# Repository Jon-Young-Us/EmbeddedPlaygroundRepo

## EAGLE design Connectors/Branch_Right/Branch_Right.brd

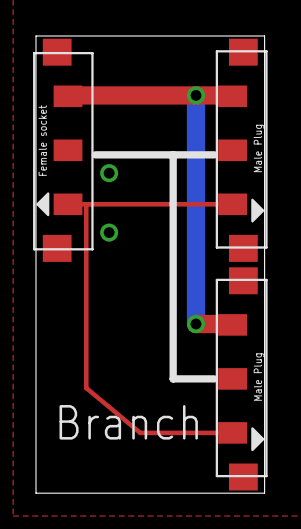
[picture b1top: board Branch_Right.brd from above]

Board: 2 copper layers, 12.7 x 25.4 mm, 3 parts (0 on the bottom side), 3 nets.

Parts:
U$1, U$4: CONN-PLUG-3POS-3MM; PLUG-3POS-3MM-SMD
U$2: CONN-SOCKET-3POS-3MM; SOCKET-3POS-3MM-SMD

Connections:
GND: U$1.GND, U$2.GND, U$4.GND
VCC: U$1.VCC, U$2.VCC, U$4.VCC
Y: U$1.SIG-OUT, U$2.SIG-IN, U$4.SIG-OUT

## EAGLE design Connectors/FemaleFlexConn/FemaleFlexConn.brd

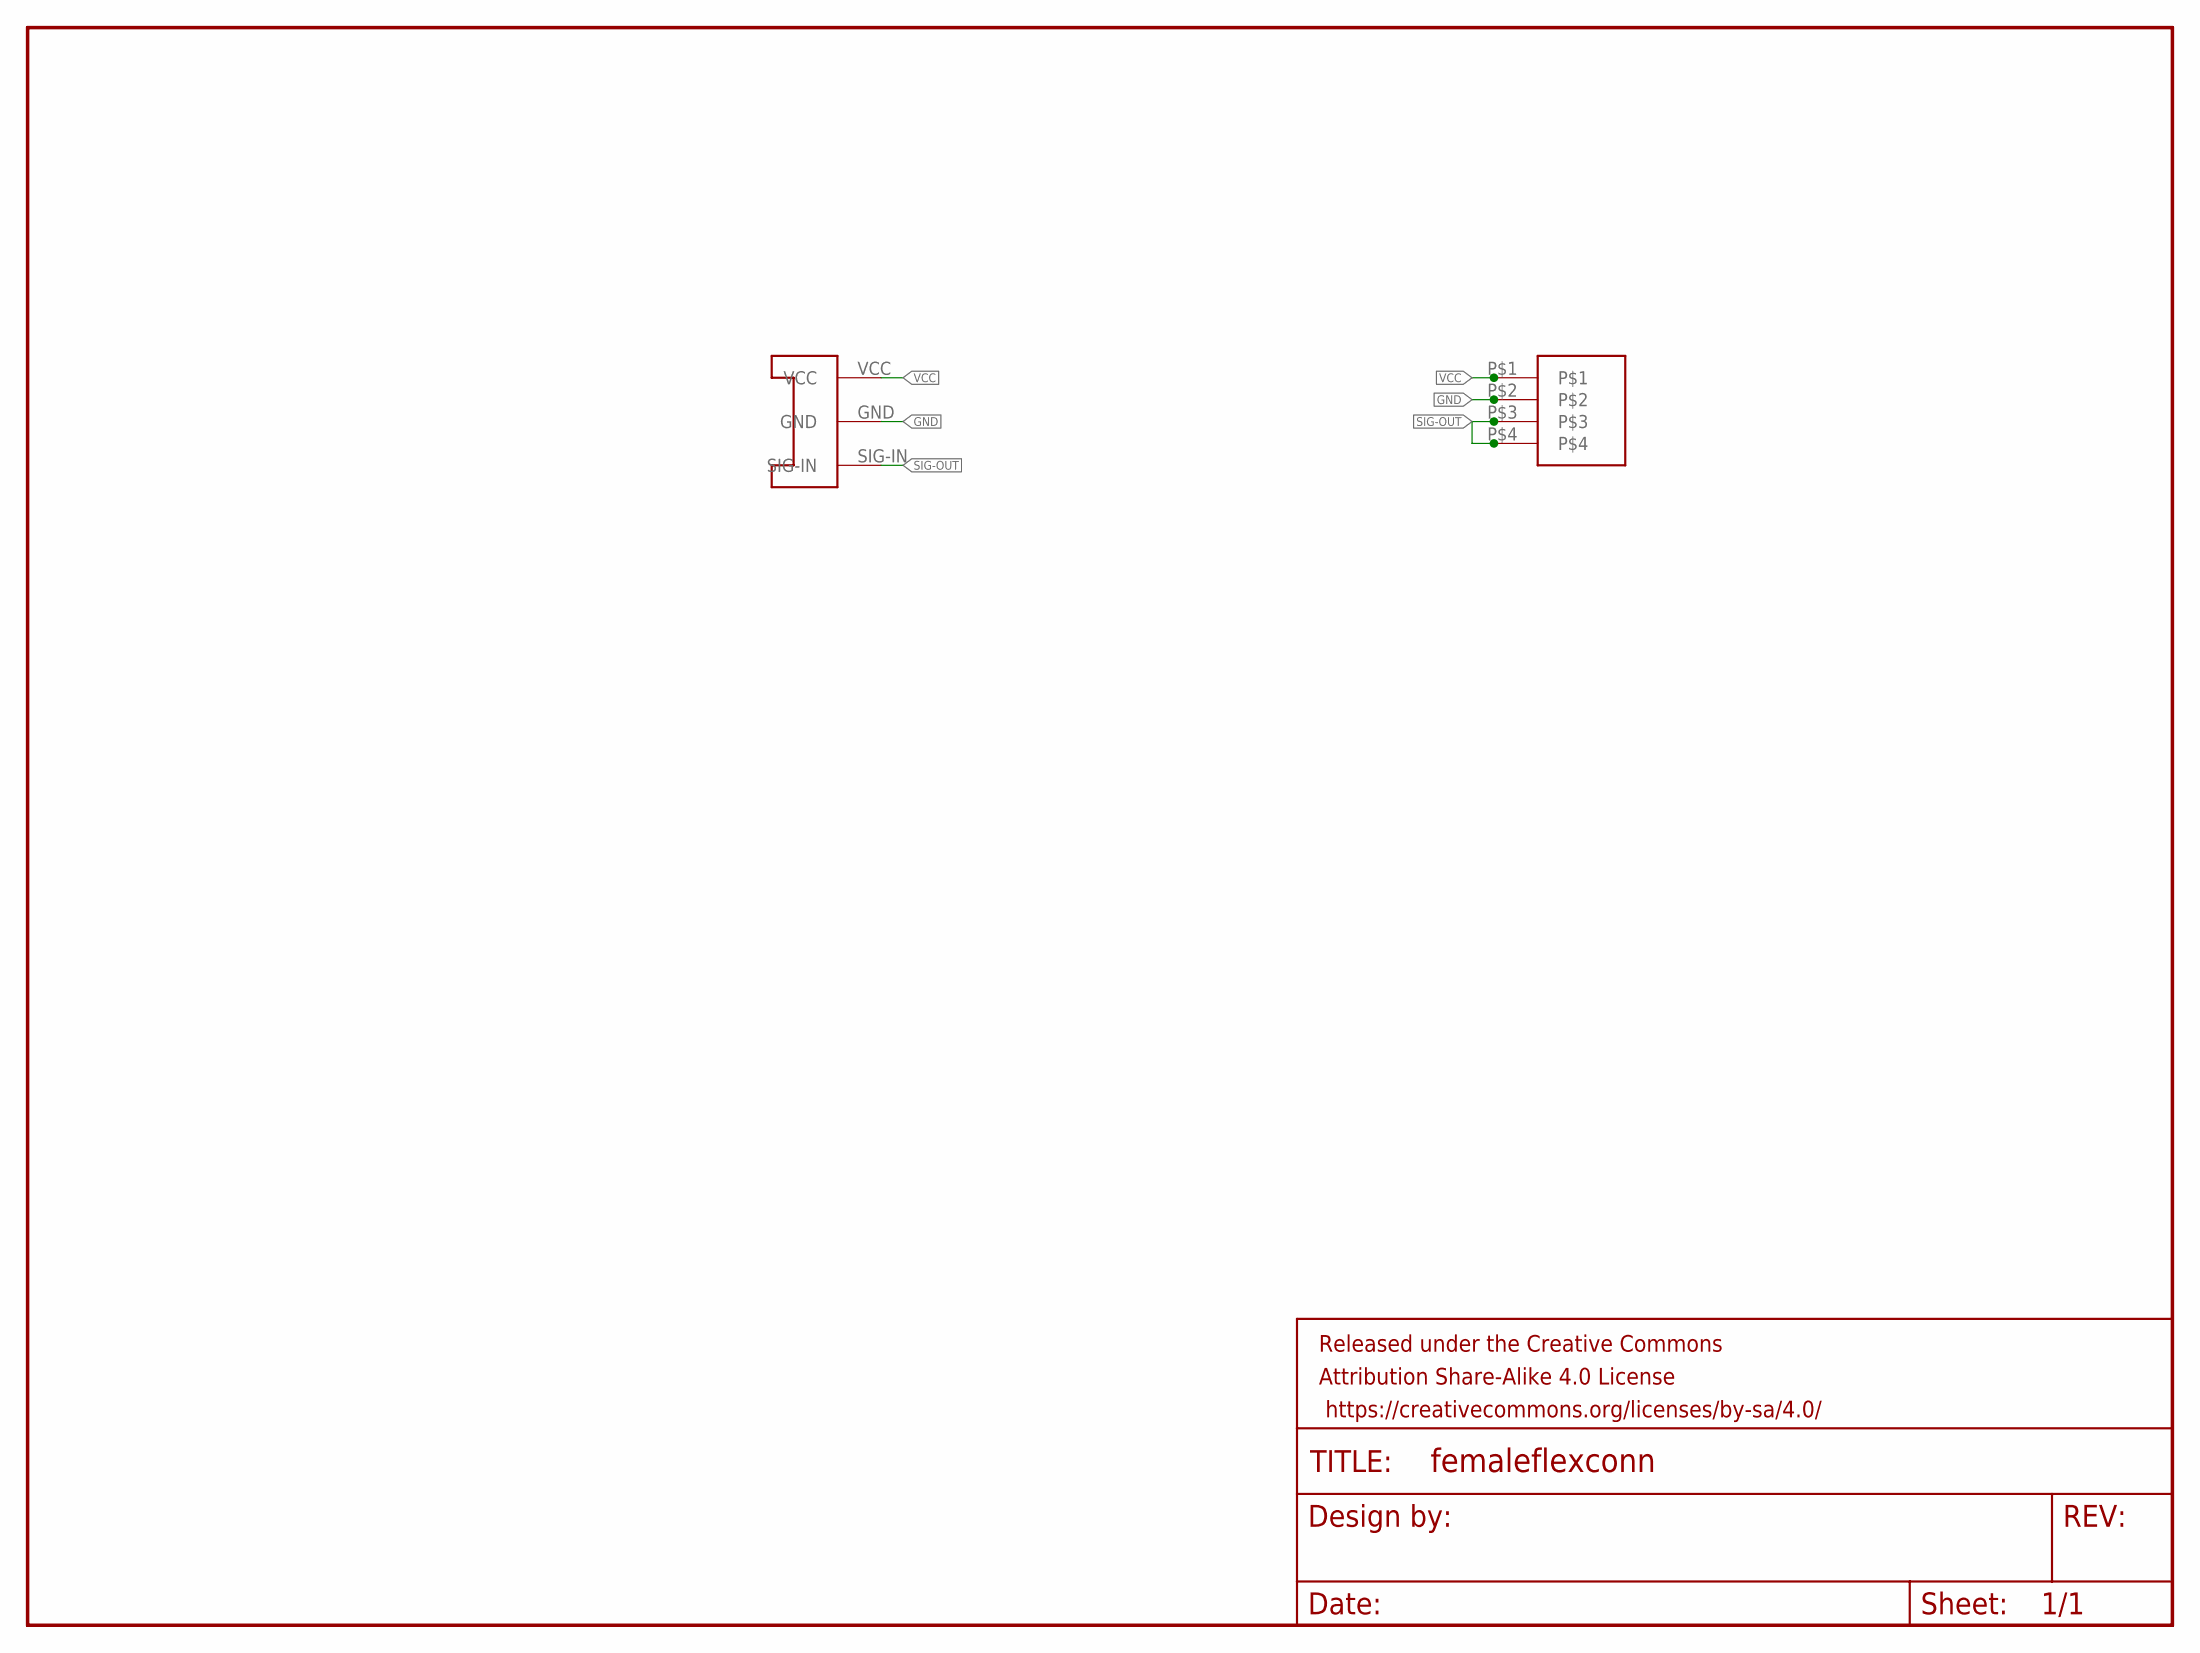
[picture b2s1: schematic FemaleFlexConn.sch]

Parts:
FRAME1: FRAME-LETTERNO_PACKAGE; DUMMY
U$1: CONN-RCPT-BLADE-4POS-4MM; RECEPT-BLAD-4MM-SMD
U$2: CONN-SOCKET-3POS-3MM; SOCKET-3POS-3MM-SMD

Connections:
GND: U$1.P$2, U$2.GND
SIG-OUT: U$1.P$3, U$1.P$4, U$2.SIG-IN
VCC: U$1.P$1, U$2.VCC

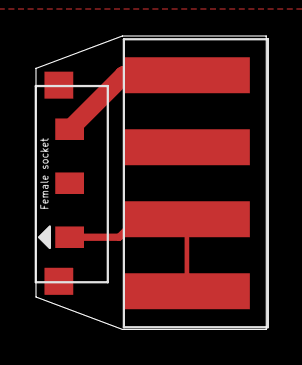
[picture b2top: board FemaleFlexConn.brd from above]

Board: 2 copper layers, 12.8 x 16.3 mm, 3 parts (0 on the bottom side), 3 nets.

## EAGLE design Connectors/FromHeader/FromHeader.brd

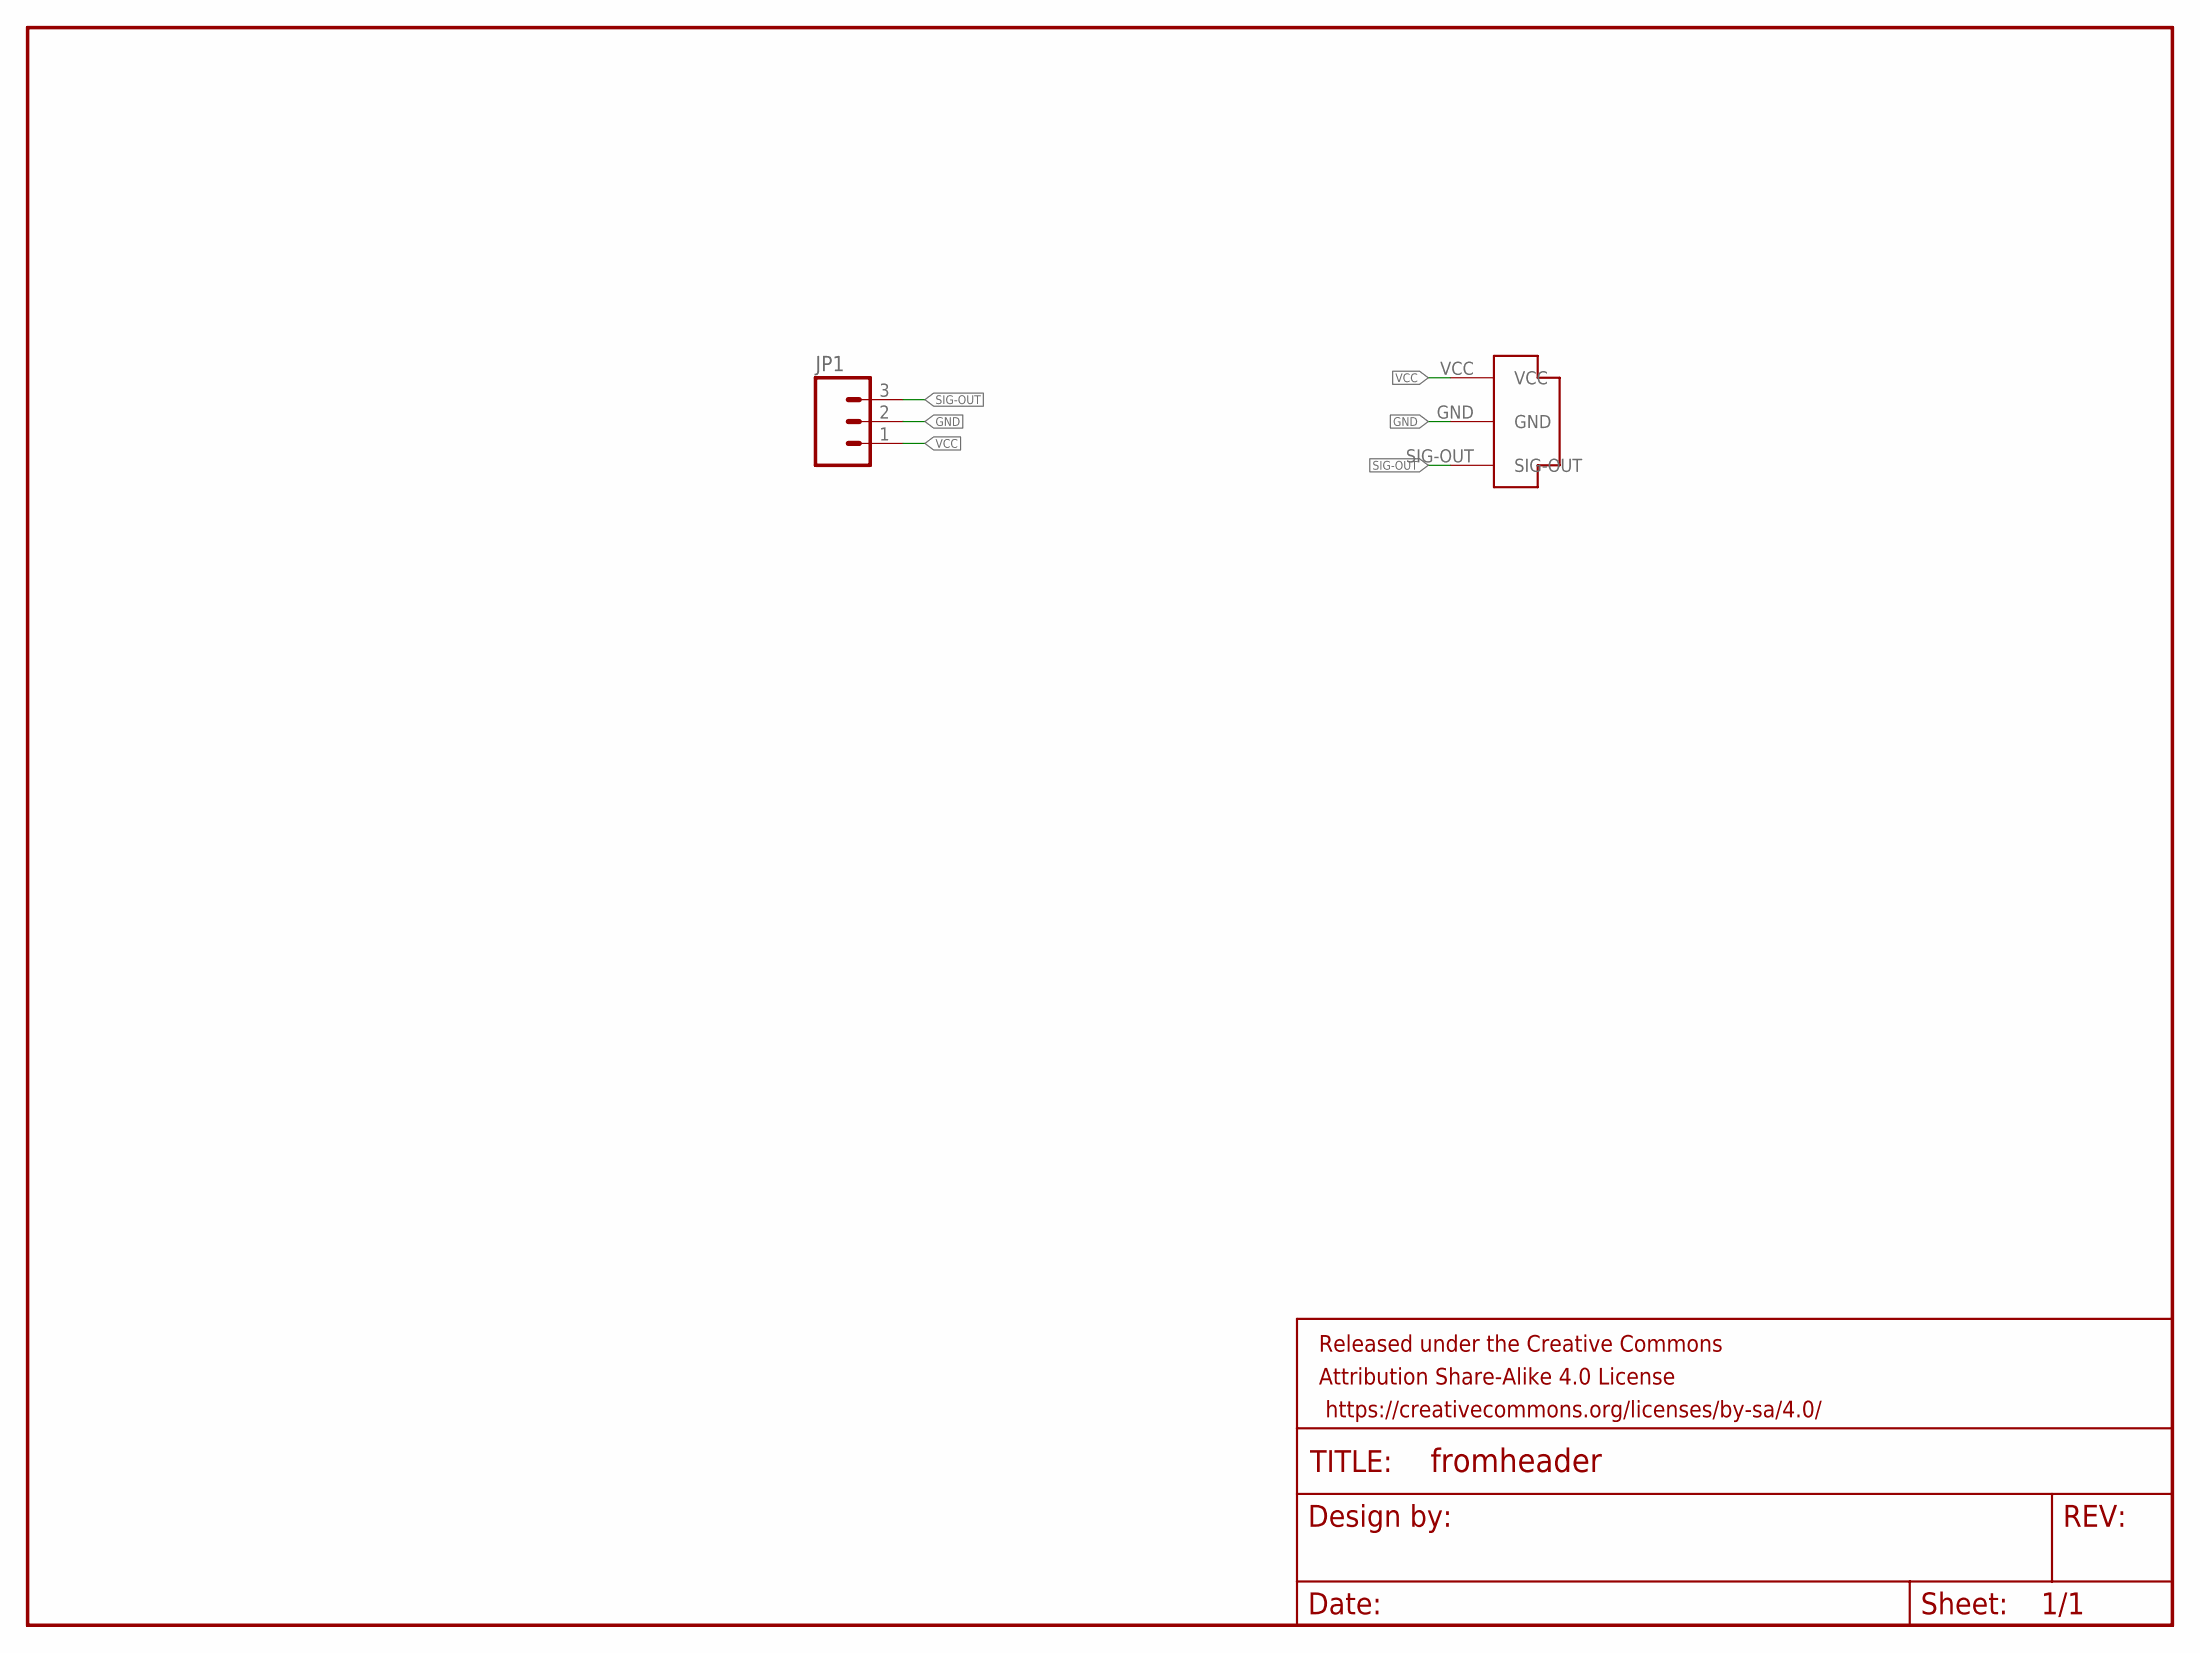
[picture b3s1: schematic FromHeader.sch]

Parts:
FRAME1: FRAME-LETTERNO_PACKAGE; DUMMY
JP1: M03LOCK; 1X03_LOCK
U$1: CONN-PLUG-3POS-3MM; PLUG-3POS-3MM-SMD

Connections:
GND: JP1.2, U$1.GND
SIG-OUT: JP1.3, U$1.SIG-OUT
VCC: JP1.1, U$1.VCC

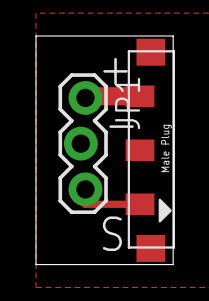
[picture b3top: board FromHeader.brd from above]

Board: 2 copper layers, 7.6 x 12.7 mm, 3 parts (0 on the bottom side), 3 nets.

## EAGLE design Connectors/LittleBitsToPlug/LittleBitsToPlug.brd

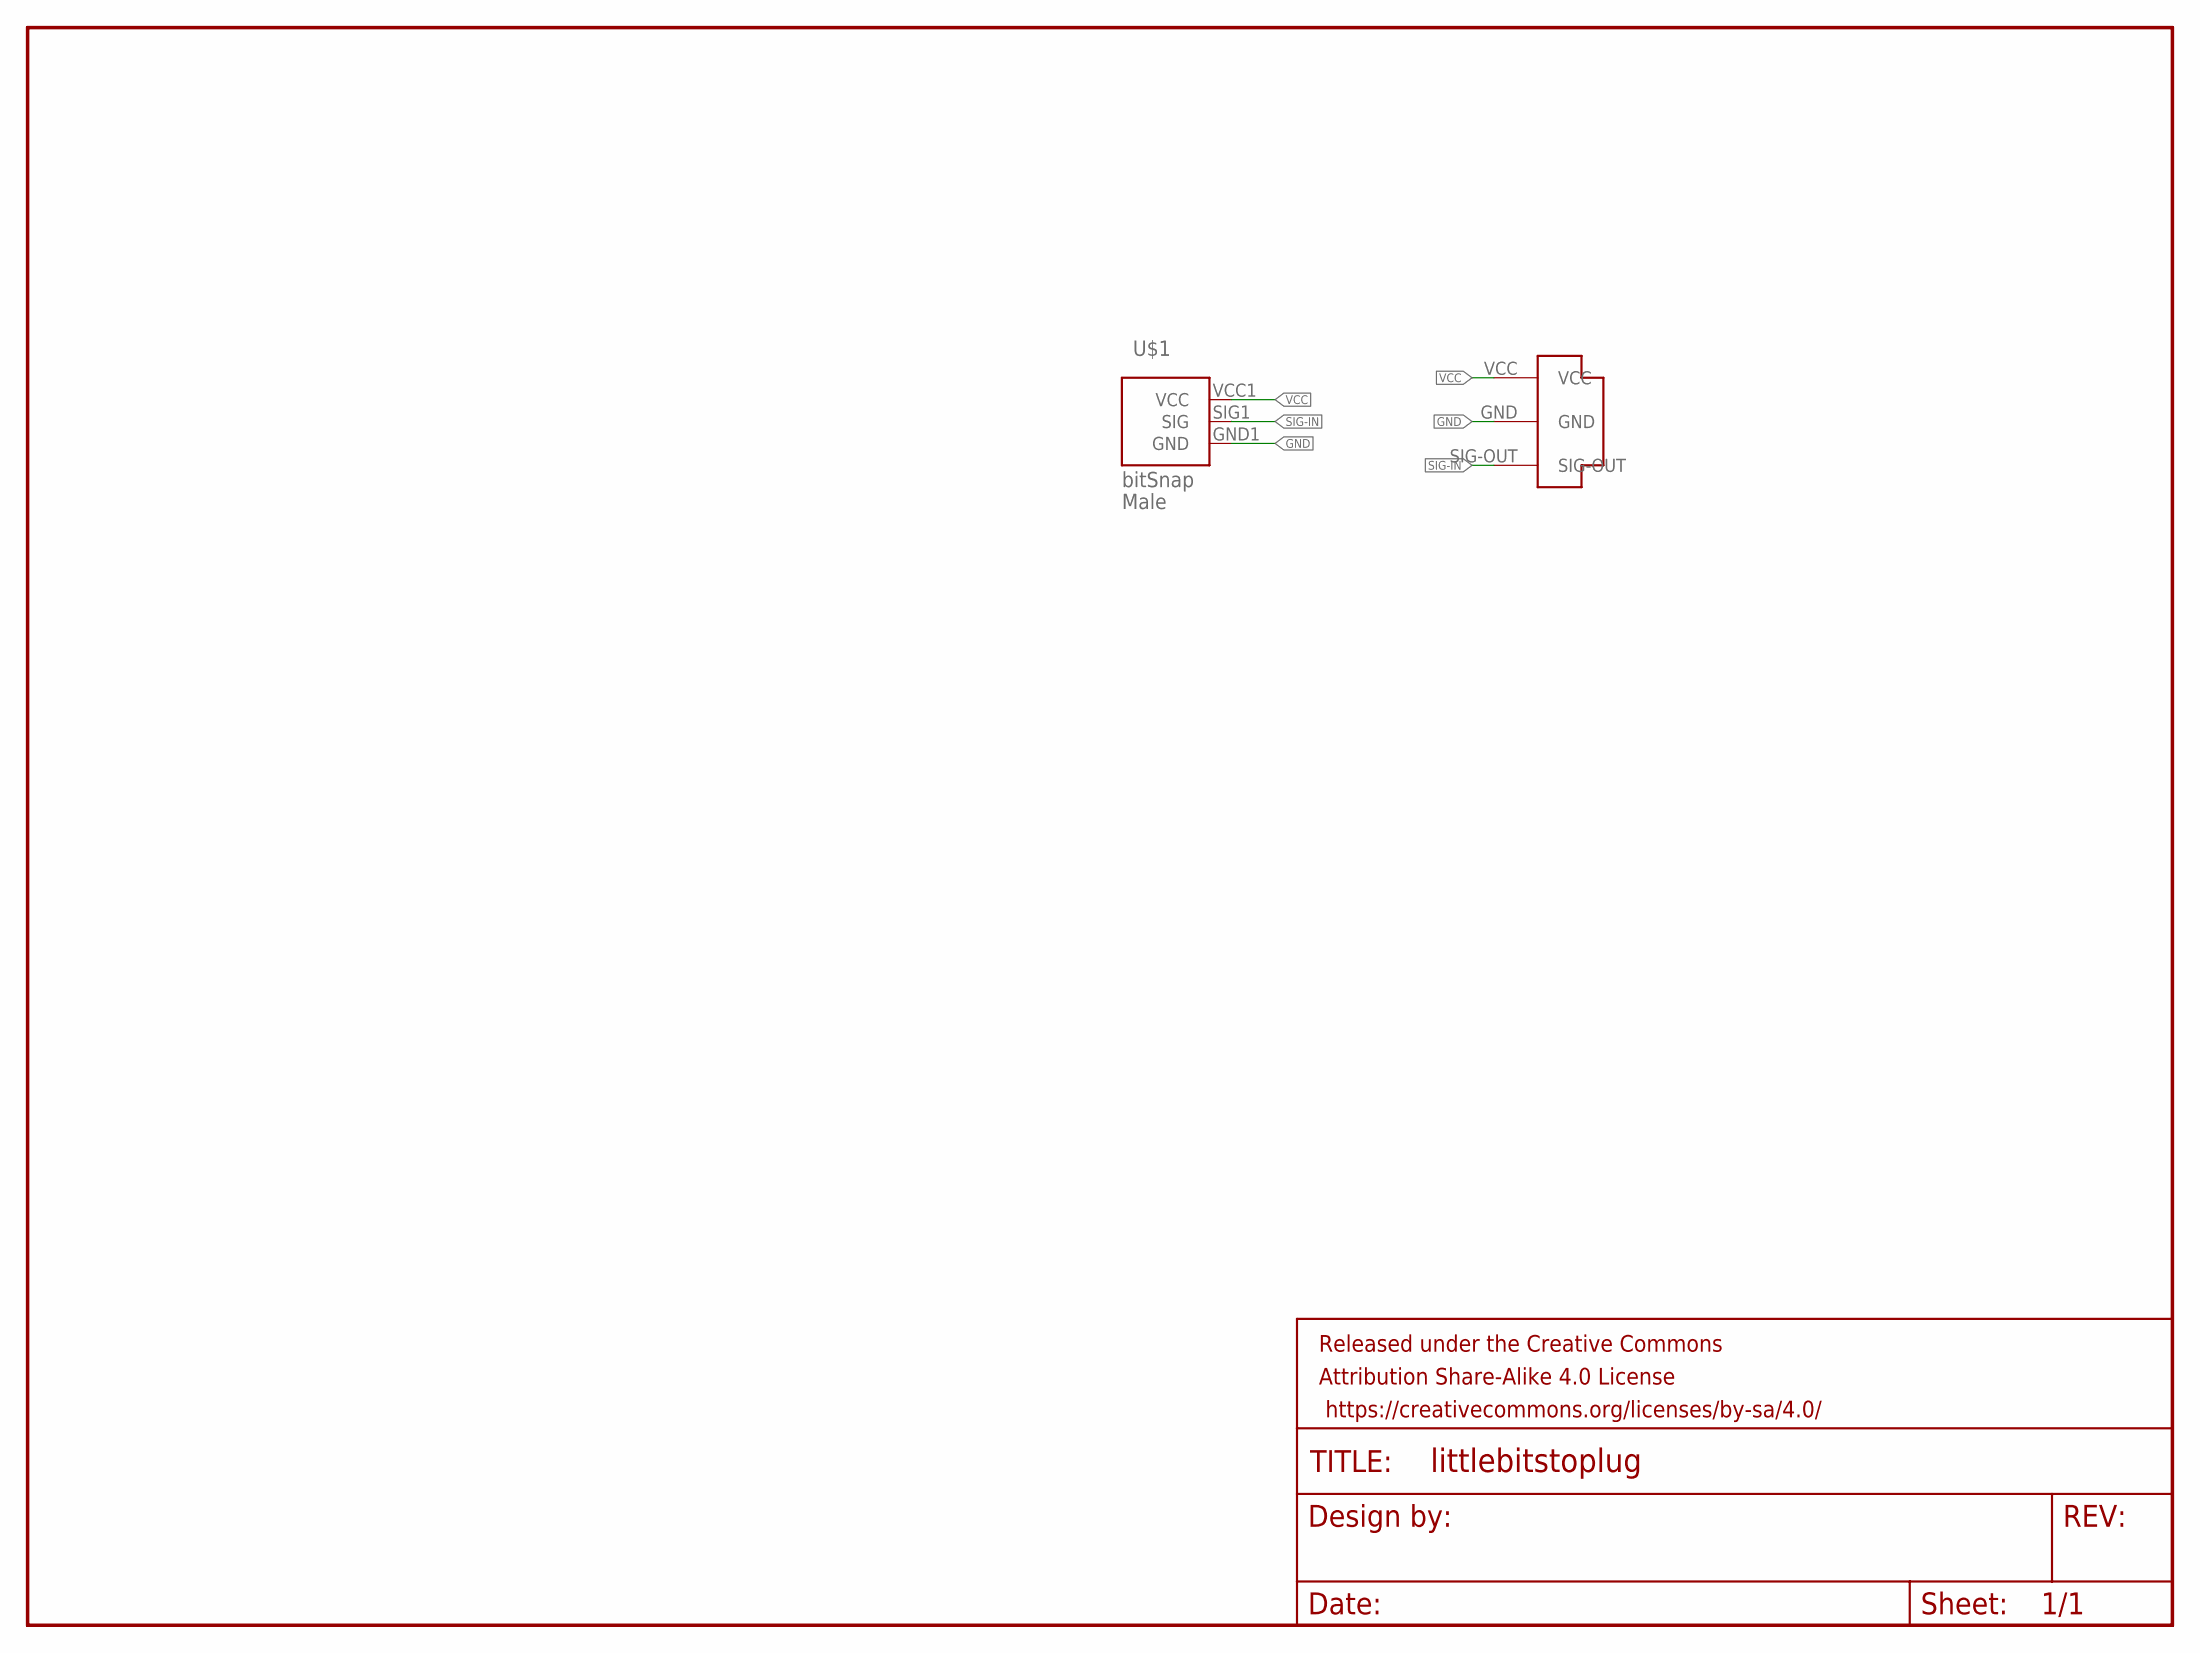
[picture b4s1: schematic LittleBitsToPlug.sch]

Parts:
FRAME1: FRAME-LETTERNO_PACKAGE; DUMMY
U$1: BITSNAP_V03_MALE
U$2: CONN-PLUG-3POS-3MM; PLUG-3POS-3MM-SMD

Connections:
GND: U$1.GND1 (GND), U$2.GND
SIG-IN: U$1.SIG1 (SIG), U$2.SIG-OUT
VCC: U$1.VCC1 (VCC), U$2.VCC

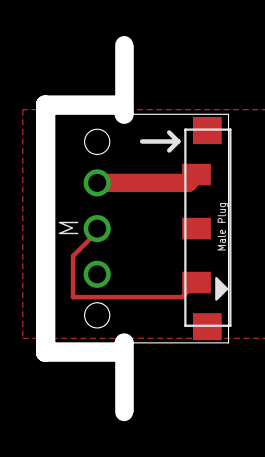
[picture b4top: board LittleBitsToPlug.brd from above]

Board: 2 copper layers, 9.7 x 12.7 mm, 3 parts (0 on the bottom side), 3 nets.

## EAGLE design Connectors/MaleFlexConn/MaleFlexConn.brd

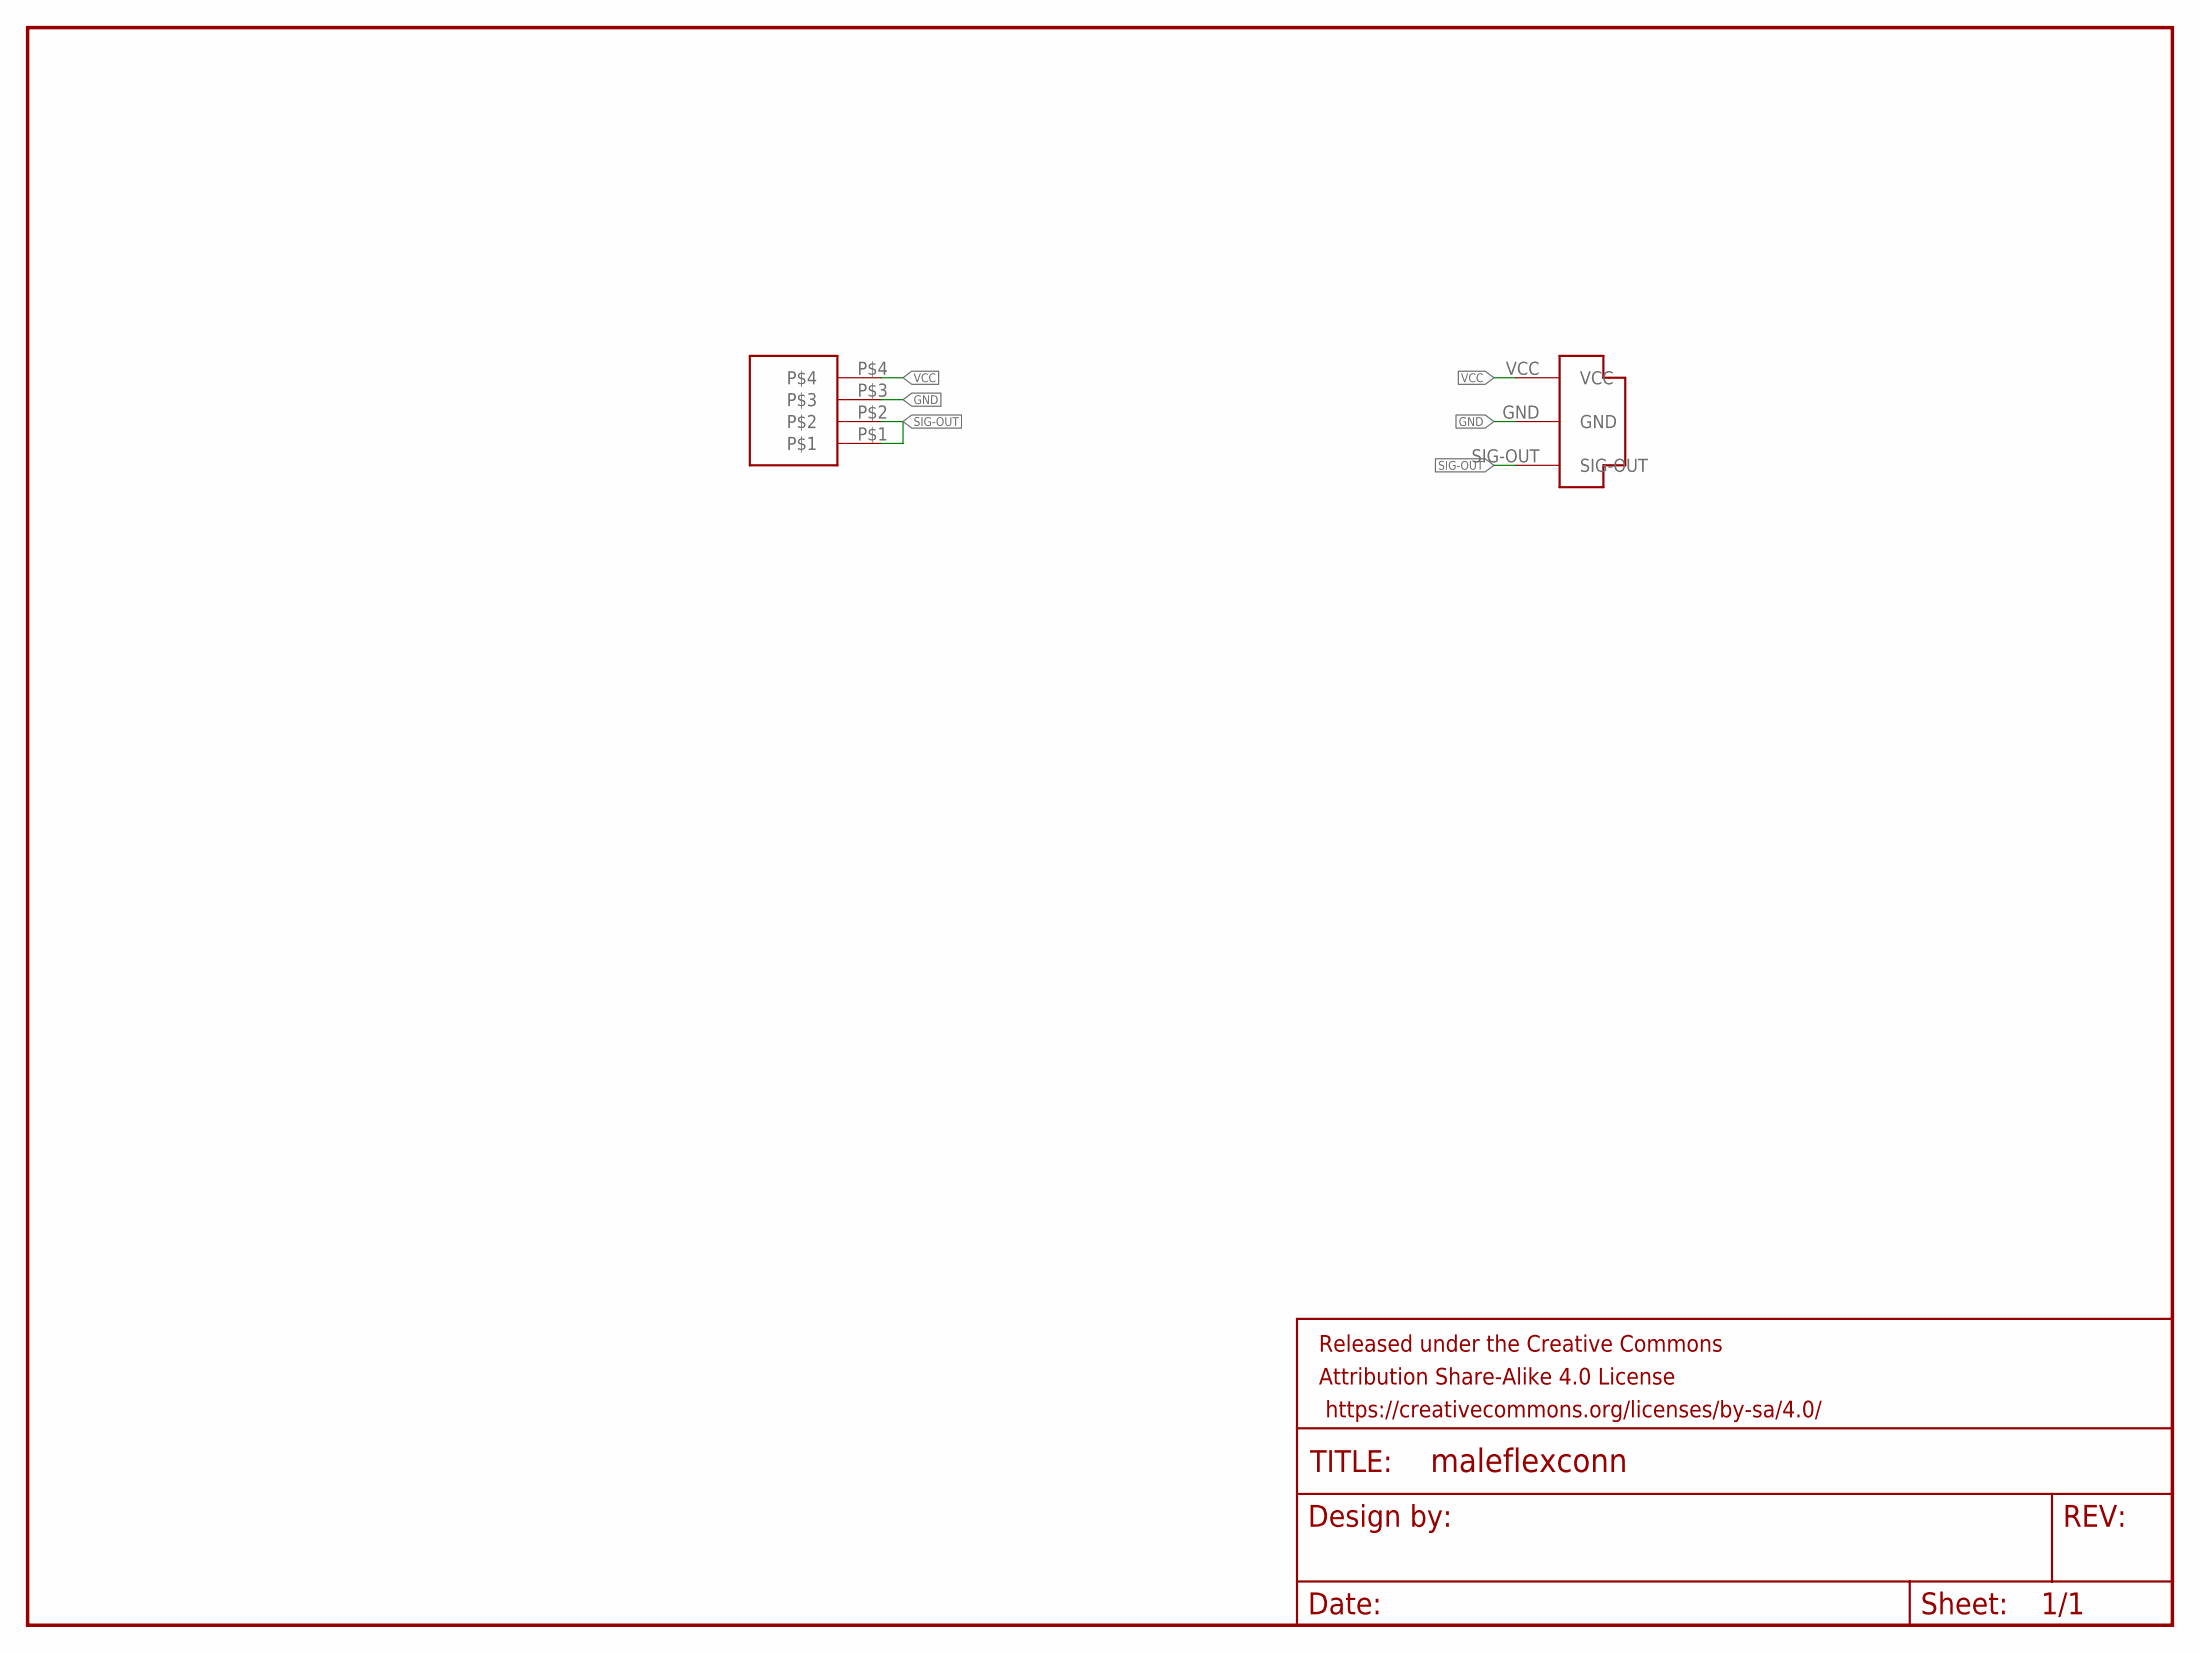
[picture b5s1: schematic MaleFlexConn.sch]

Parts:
FRAME1: FRAME-LETTERNO_PACKAGE; DUMMY
U$1: CONN-PLUG-3POS-3MM; PLUG-3POS-3MM-SMD
U$2: CONN-RCPT-BLADE-4POS-4MM; RECEPT-BLAD-4MM-SMD

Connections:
GND: U$1.GND, U$2.P$3
SIG-OUT: U$1.SIG-OUT, U$2.P$1, U$2.P$2
VCC: U$1.VCC, U$2.P$4

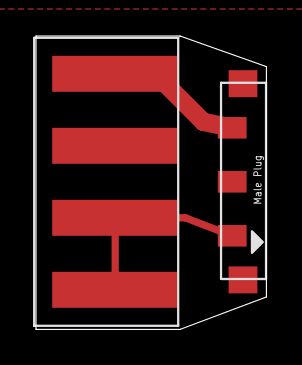
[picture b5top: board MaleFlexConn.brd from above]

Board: 2 copper layers, 12.8 x 16.3 mm, 3 parts (0 on the bottom side), 3 nets.

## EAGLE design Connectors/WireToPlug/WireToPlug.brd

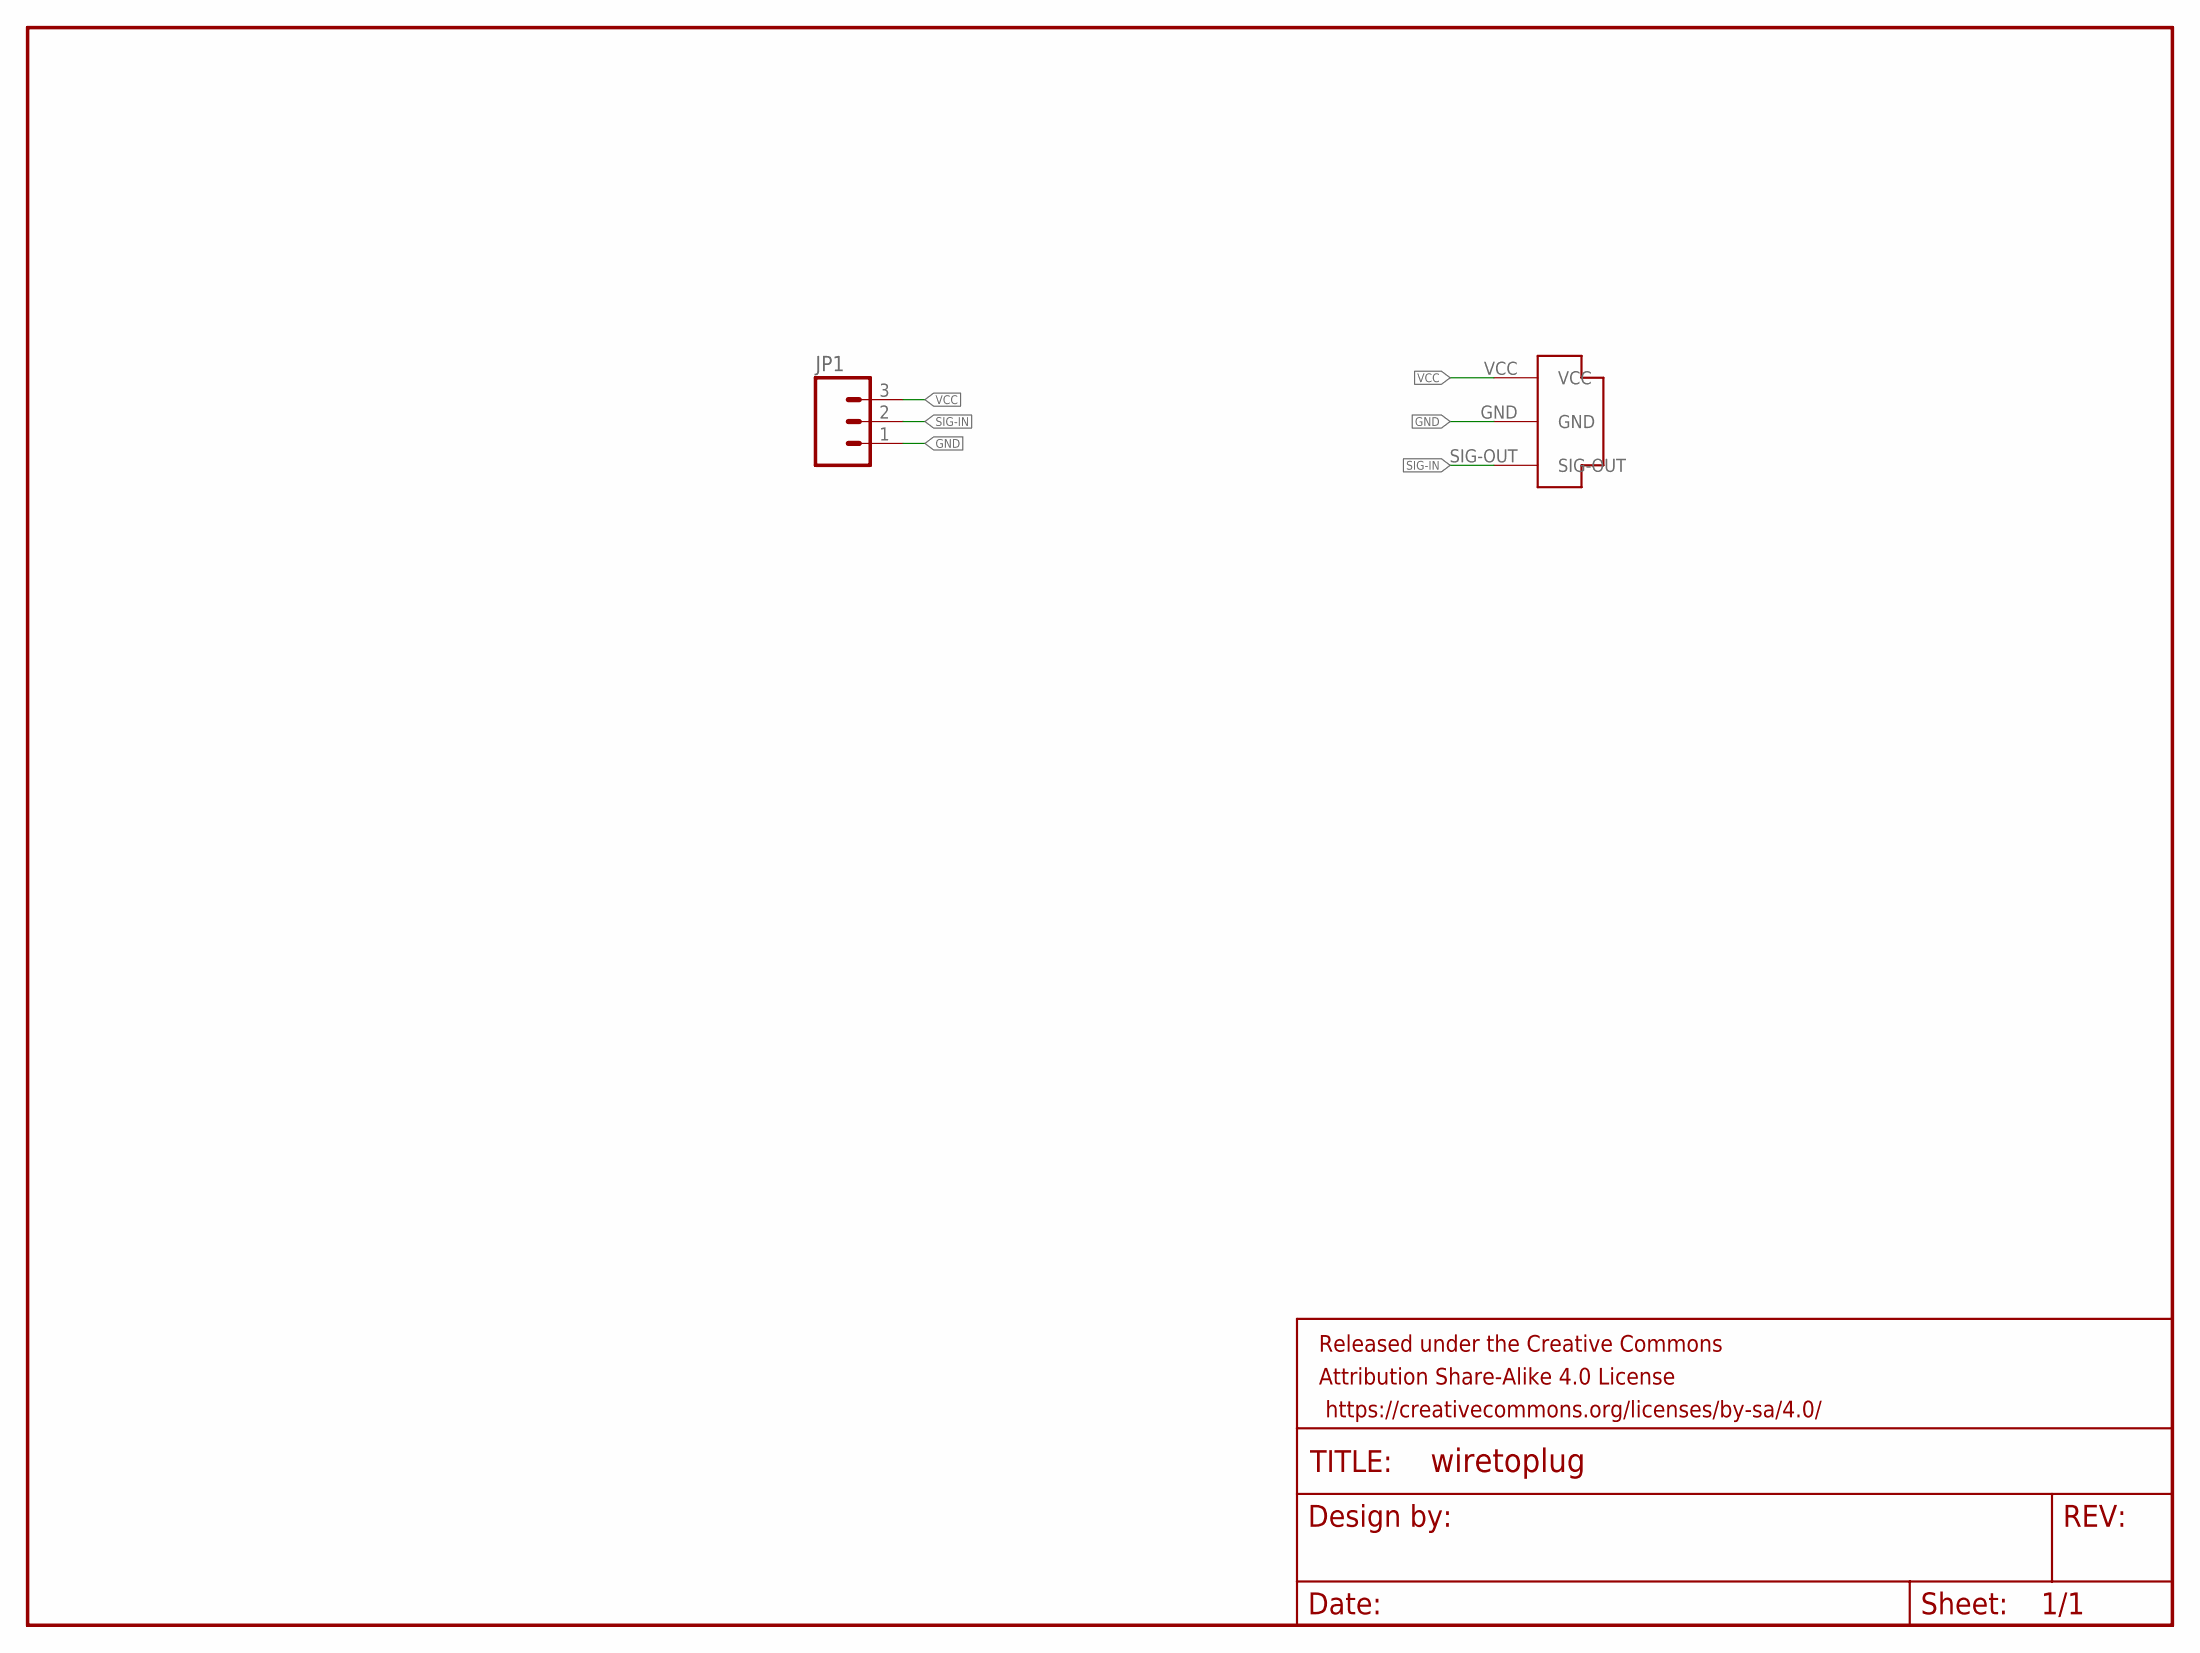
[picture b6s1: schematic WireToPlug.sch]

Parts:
FRAME1: FRAME-LETTERNO_PACKAGE; DUMMY
JP1: M03SMD; 1X03-1MM-RA
U$1: CONN-PLUG-3POS-3MM; PLUG-3POS-3MM-SMD

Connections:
GND: JP1.1, U$1.GND
SIG-IN: JP1.2, U$1.SIG-OUT
VCC: JP1.3, U$1.VCC

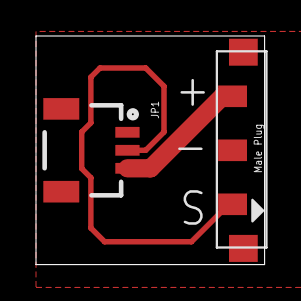
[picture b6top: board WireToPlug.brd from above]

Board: 2 copper layers, 12.7 x 12.7 mm, 3 parts (0 on the bottom side), 3 nets.

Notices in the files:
parts and their libraries:
SparkFun-Aesthetics: Licensing: Creative Commons ShareAlike 4.0 International - https://creativecommons.org/licenses/by-sa/4.0
SparkFun-Aesthetics: Released under the Creative Commons Attribution Share-Alike 4.0 License
SparkFun-Aesthetics: https://creativecommons.org/licenses/by-sa/4.0
